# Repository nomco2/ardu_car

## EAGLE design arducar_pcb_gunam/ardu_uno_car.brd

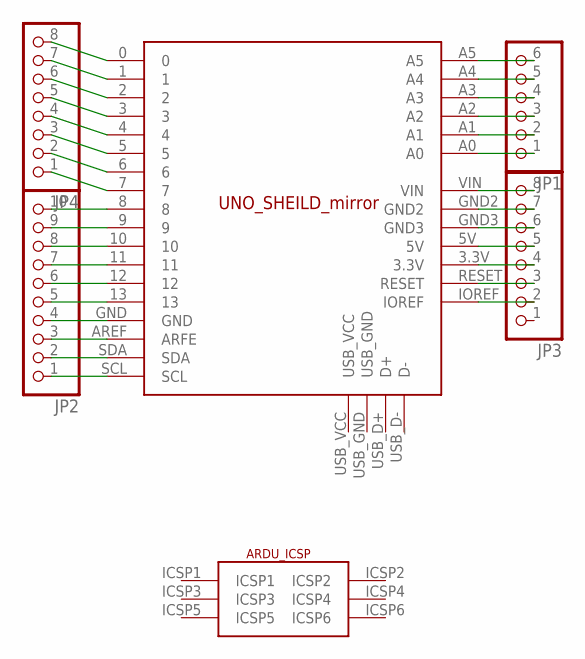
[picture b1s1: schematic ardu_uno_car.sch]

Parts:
JP1: PINHEAD_PINHD-1X6; PINHEAD_1X06
JP2: PINHD-1X10; 1X10
JP3, JP4: PINHEAD_PINHD-1X8; PINHEAD_1X08
U$1: UNO_SHEILD_MIRROR_CH_VER

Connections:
unnamed: JP2.1, U$1.SCL
unnamed: JP2.2, U$1.SDA
unnamed: JP2.3, U$1.AREF (ARFE)
unnamed: JP2.4, U$1.GND
unnamed: JP2.5, U$1.13
unnamed: JP2.6, U$1.12
unnamed: JP2.7, U$1.11
unnamed: JP2.8, U$1.10
unnamed: JP2.9, U$1.9
unnamed: JP2.10, U$1.8
unnamed: JP4.1, U$1.7
unnamed: JP4.2, U$1.6
unnamed: JP4.3, U$1.5
unnamed: JP4.4, U$1.4
unnamed: JP4.5, U$1.3
unnamed: JP4.6, U$1.2
unnamed: JP4.7, U$1.1
unnamed: JP4.8, U$1.0
unnamed: JP1.1, U$1.A0
unnamed: JP1.2, U$1.A1
unnamed: JP1.3, U$1.A2
unnamed: JP1.4, U$1.A3
unnamed: JP1.5, U$1.A4
unnamed: JP1.6, U$1.A5
unnamed: JP3.2, U$1.IOREF
unnamed: JP3.3, U$1.RESET
unnamed: JP3.4, U$1.3.3V
unnamed: JP3.5, U$1.5V
unnamed: JP3.6, U$1.GND3
unnamed: JP3.7, U$1.GND2
unnamed: JP3.8, U$1.VIN

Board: 2 copper layers, 5 parts (0 on the bottom side), 31 nets, no tracks yet.

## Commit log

2017-10-23 first_saved
2017-10-23 movable_add
2017-10-23 button1_image_add
2017-10-25 move_text_invisible
2017-10-25 data_saving_operation_dev_not_complite
2017-10-29 get_address_function
2017-11-11 auto_creating_operation_buttons
2017-11-14 buttons_auto_creating_add
2022-02-26 ki cad
